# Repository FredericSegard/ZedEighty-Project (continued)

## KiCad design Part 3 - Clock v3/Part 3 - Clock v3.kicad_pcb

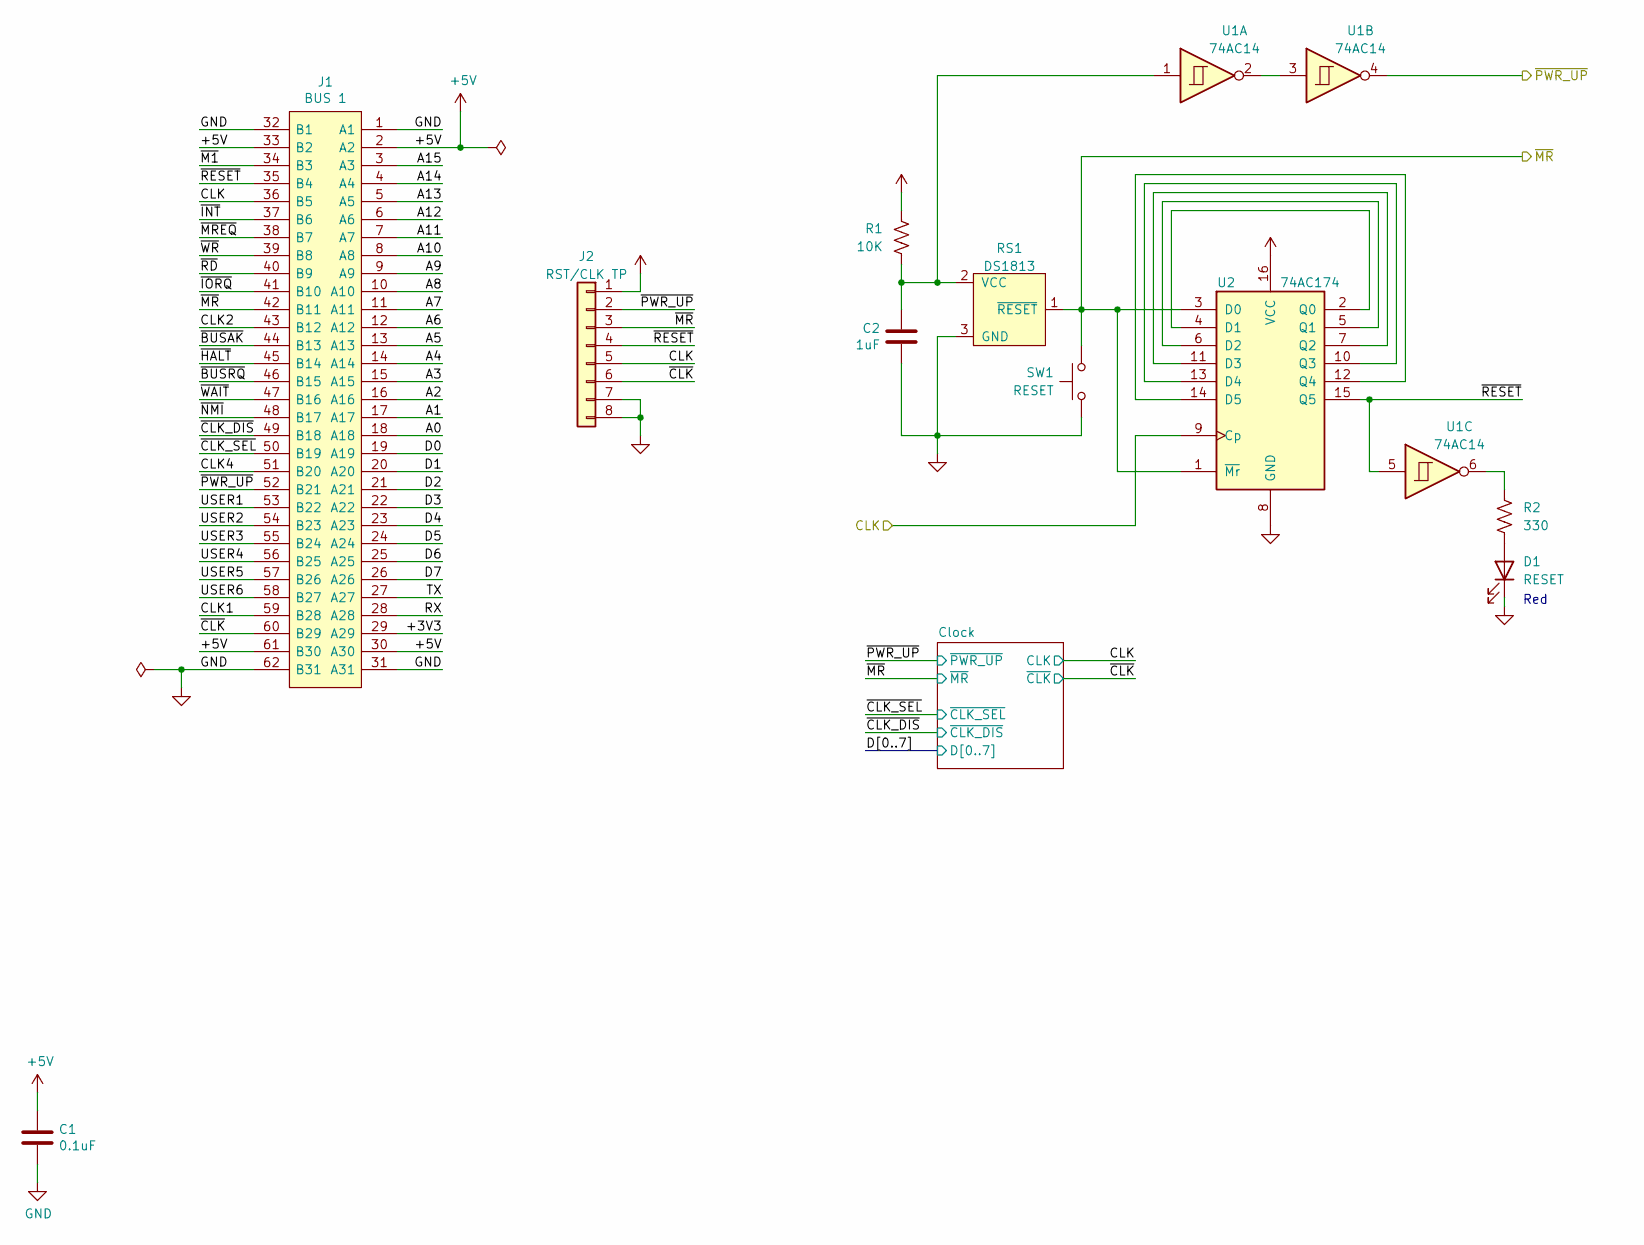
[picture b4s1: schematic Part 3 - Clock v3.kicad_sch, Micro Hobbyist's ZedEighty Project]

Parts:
C1: 0.1uF; C_Disc_D3.0mm_W2.0mm_P2.50mm
C2: 1uF; C_Disc_D3.0mm_W2.0mm_P2.50mm
D1: RESET; LED_D3.0mm_Horizontal_O1.27mm_Z2.0mm_Clear
J1: BUS 1; BUS_XT; Mouser Part Number 571-6-5530843-5
J2: RST/CLK TP; PinHeader_1x08_P2.54mm_Horizontal
R1: 10K; R_Axial_DIN0207_L6.3mm_D2.5mm_P10.16mm_Horizontal
R2: 330; R_Axial_DIN0207_L6.3mm_D2.5mm_P10.16mm_Horizontal
RS1: DS1813; TO-92L_Inline_Wide
SW1: RESET; SW_Tactile_SPST_Angled_PTS645Vx58-2LFS
U1: 74AC14; DIP-14_W7.62mm_Socket
U2: 74AC174; DIP-16_W7.62mm_Socket

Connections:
/+3V3: J1.29 (A29)
/A0: J1.18 (A18)
/A1: J1.17 (A17)
/A2: J1.16 (A16)
/A3: J1.15 (A15)
/A4: J1.14 (A14)
/A5: J1.13 (A13)
/A6: J1.12 (A12)
/A7: J1.11 (A11)
/A8: J1.10 (A10)
/A9: J1.9 (A9)
/A10: J1.8 (A8)
/A11: J1.7 (A7)
/A12: J1.6 (A6)
/A13: J1.5 (A5)
/A14: J1.4 (A4)
/A15: J1.3 (A3)
/CLK: J1.36 (B5), J2.5, U2.9 (Cp); also elsewhere on the board
/CLK1: J1.59 (B28)
/CLK2: J1.43 (B12)
/CLK4: J1.51 (B20)
/D0: J1.19 (A19); also elsewhere on the board
/D1: J1.20 (A20); also elsewhere on the board
/D2: J1.21 (A21)
/D3: J1.22 (A22)
/D4: J1.23 (A23)
/D5: J1.24 (A24)
/D6: J1.25 (A25)
/D7: J1.26 (A26)
/RX: J1.28 (A28)
/TX: J1.27 (A27)
/USER1: J1.53 (B22)
/USER2: J1.54 (B23)
/USER3: J1.55 (B24)
/USER4: J1.56 (B25)
/USER5: J1.57 (B26)
/USER6: J1.58 (B27)
/~BUSAK: J1.44 (B13)
/~BUSRQ: J1.46 (B15)
/~CLK_DIS: J1.49 (B18); also elsewhere on the board
/~CLK_SEL: J1.50 (B19); also elsewhere on the board
/~CLK: J1.60 (B29), J2.6; also elsewhere on the board
/~HALT: J1.45 (B14)
/~INT: J1.37 (B6)
/~IORQ: J1.41 (B10)
/~M1: J1.34 (B3)
/~MREQ: J1.38 (B7)
/~MR: J1.42 (B11), J2.3, RS1.1 (~RESET), SW1.1, U2.1 (~Mr), U2.3 (D0); also elsewhere on the board
/~NMI: J1.48 (B17)
/~PWR_UP: J1.52 (B21), J2.2, U1.4; also elsewhere on the board
/~RD: J1.40 (B9)
/~RESET: J1.35 (B4), J2.4, U1.5, U2.15 (Q5)
/~WAIT: J1.47 (B16)
/~WR: J1.39 (B8)
unnamed: C2.1, R1.1, RS1.2 (VCC), U1.1
unnamed: D1.2 (A), R2.2
unnamed: R2.1, U1.6
unnamed: U1.2, U1.3
unnamed: U2.2 (Q0), U2.4 (D1)
unnamed: U2.5 (Q1), U2.6 (D2)
unnamed: U2.10 (Q3), U2.13 (D4)
unnamed: U2.7 (Q2), U2.11 (D3)
unnamed: U2.12 (Q4), U2.14 (D5)

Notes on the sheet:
Red

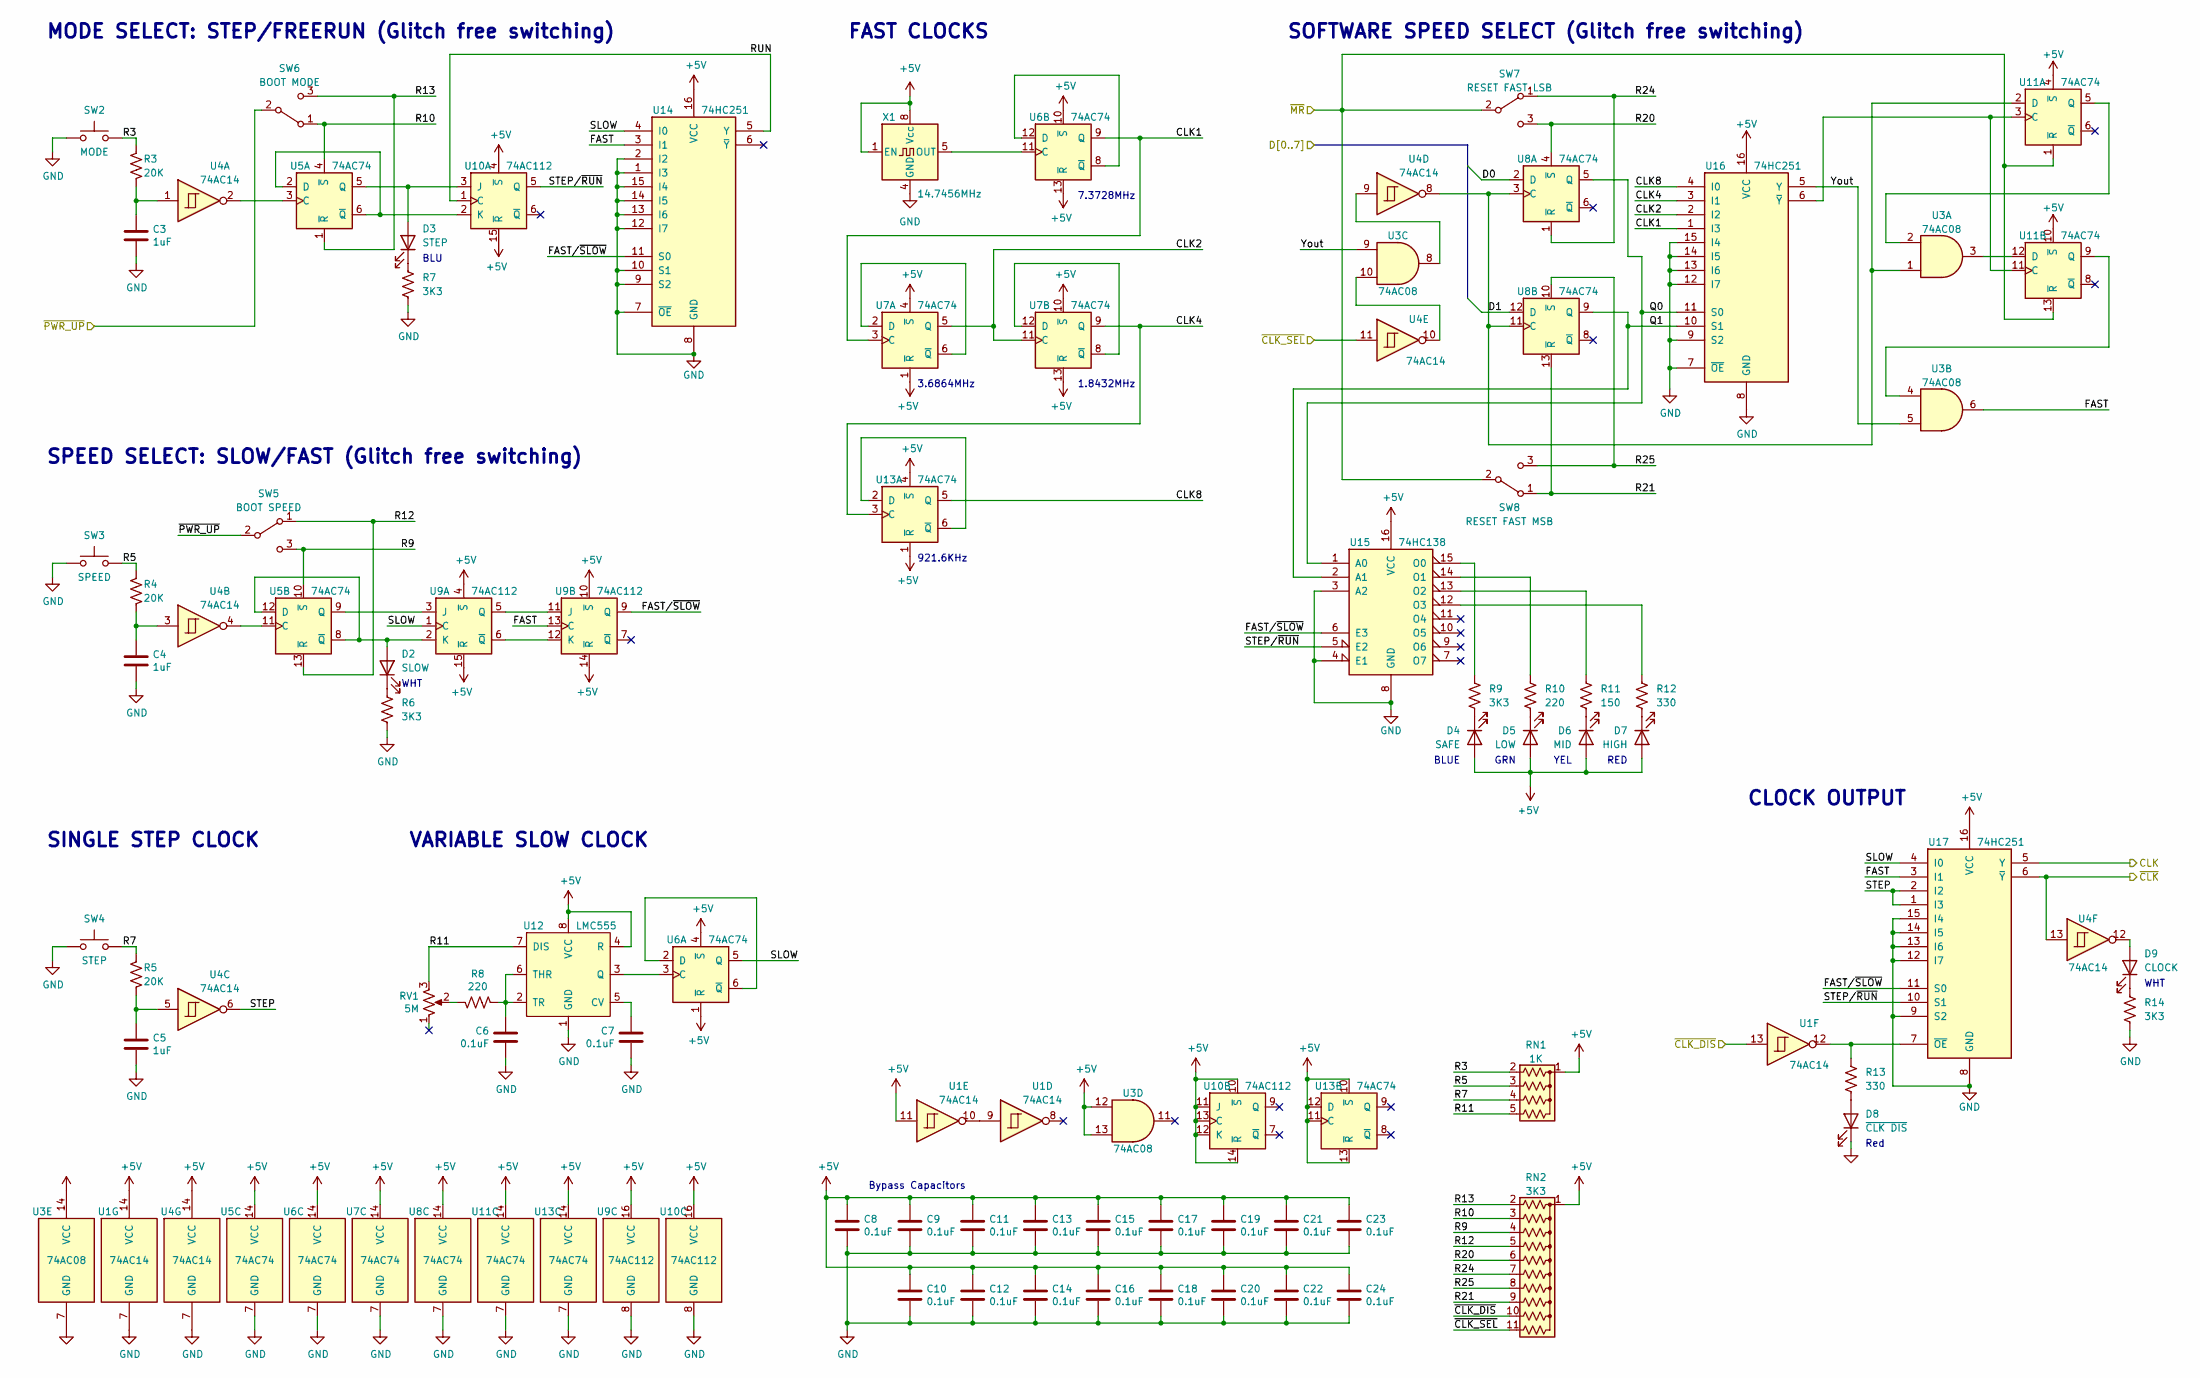
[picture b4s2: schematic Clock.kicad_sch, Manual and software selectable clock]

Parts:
C3, C4, C5: 1uF; C_Disc_D3.0mm_W1.6mm_P2.50mm
C6, C7, C8, C9, C10, C11, C12, C13, C14, C15, C16, C17, C18, C19, C20, C21, C22, C23, C24: 0.1uF; C_Disc_D3.0mm_W1.6mm_P2.50mm
D2: SLOW; LED_D3.0mm_Horizontal_O1.27mm_Z2.0mm_Clear
D3: STEP; LED_D3.0mm_Horizontal_O1.27mm_Z2.0mm_Clear
D4: SAFE; LED_D3.0mm_Horizontal_O1.27mm_Z2.0mm_Clear
D5: LOW; LED_D3.0mm_Horizontal_O1.27mm_Z2.0mm_Clear
D6: MID; LED_D3.0mm_Horizontal_O1.27mm_Z2.0mm_Clear
D7: HIGH; LED_D3.0mm_Horizontal_O1.27mm_Z2.0mm_Clear
D8: ~{CLK DIS}; LED_D3.0mm_Horizontal_O1.27mm_Z2.0mm_Clear
D9: CLOCK; LED_D3.0mm_Horizontal_O1.27mm_Z2.0mm_Clear
R3, R4, R5: 20K; R_Axial_DIN0207_L6.3mm_D2.5mm_P10.16mm_Horizontal
R6, R7, R9, R14: 3K3; R_Axial_DIN0207_L6.3mm_D2.5mm_P10.16mm_Horizontal
R8, R10: 220; R_Axial_DIN0207_L6.3mm_D2.5mm_P10.16mm_Horizontal
R11: 150; R_Axial_DIN0207_L6.3mm_D2.5mm_P10.16mm_Horizontal
R12, R13: 330; R_Axial_DIN0207_L6.3mm_D2.5mm_P10.16mm_Horizontal
RN1: 1K; R_Array_SIP5
RN2: 3K3; R_Array_SIP11
RV1: 5M; Potentiometer_Bourns_3296Z_Horizontal
SW2: MODE; SW_Tactile_SPST_Angled_PTS645Vx58-2LFS
SW3: SPEED; SW_Tactile_SPST_Angled_PTS645Vx58-2LFS
SW4: STEP; SW_Tactile_SPST_Angled_PTS645Vx58-2LFS
SW5: BOOT SPEED; Microswitch_4.7mm_spacing
SW6: BOOT MODE; Microswitch_4.7mm_spacing
SW7: RESET FAST LSB; Microswitch_4.7mm_spacing
SW8: RESET FAST MSB; Microswitch_4.7mm_spacing
U1, U4: 74AC14; DIP-14_W7.62mm_Socket
U3: 74AC08; DIP-14_W7.62mm_Socket
U5, U6, U7, U8, U11, U13: 74AC74; DIP-14_W7.62mm_Socket
U9, U10: 74AC112; DIP-16_W7.62mm_Socket
U12: LMC555; DIP-8_W7.62mm_Socket
U14, U16, U17: 74HC251; DIP-16_W7.62mm_Socket
U15: 74HC138; DIP-16_W7.62mm_Socket
X1: 14.7456MHz; DIP-8-4_W7.62mm_Oscillator_Socket

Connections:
/CLK: U17.5 (Y); also elsewhere on the board
/Clock/CLK1: U6.9 (Q), U7.3 (C), U16.1 (I3)
/Clock/CLK2: U7.5 (Q), U7.11 (C), U16.2 (I2)
/Clock/CLK4: U7.9 (Q), U13.3 (C), U16.3 (I1)
/Clock/CLK8: U13.5 (Q), U16.4 (I0)
/Clock/FAST: U3.6, U9.13 (C), U14.3 (I1), U17.3 (I1)
/Clock/FAST/~SLOW: U9.9 (Q), U14.11 (S0), U15.6 (E3), U17.11 (S0)
/Clock/Q0: U8.5 (Q), U15.1 (A0), U16.11 (S0)
/Clock/Q1: U8.9 (Q), U15.2 (A1), U16.10 (S1)
/Clock/R3: R3.2, RN1.2 (R1), SW2.1
/Clock/R5: R4.2, RN1.3 (R2), SW3.1
/Clock/R7: R5.2, RN1.4 (R3), SW4.1
/Clock/R9: RN2.4 (R3), SW5.3 (C), U5.10 (~S)
/Clock/R10: RN2.3 (R2), SW6.1 (A), U5.4 (~S)
/Clock/R11: RN1.5 (R4), RV1.3, U12.7 (DIS)
/Clock/R12: RN2.5 (R4), SW5.1 (A), U5.13 (~R)
/Clock/R13: RN2.2 (R1), SW6.3 (C), U5.1 (~R)
/Clock/R20: RN2.6 (R5), SW7.3 (C), U8.4 (~S)
/Clock/R21: RN2.9 (R8), SW8.1 (A), U8.13 (~R)
/Clock/R24: RN2.7 (R6), SW7.1 (A), U8.1 (~R)
/Clock/R25: RN2.8 (R7), SW8.3 (C), U8.10 (~S)
/Clock/RUN: U10.1 (C), U14.5 (Y)
/Clock/SLOW: U6.5 (Q), U9.1 (C), U14.4 (I0), U17.4 (I0)
/Clock/STEP: U4.6, U17.1 (I3), U17.2 (I2)
/Clock/STEP/~RUN: U10.5 (Q), U15.5 (E2), U17.10 (S1)
/Clock/Yout: U3.5, U3.9, U16.5 (Y)
/D0: U8.2 (D); also elsewhere on the board
/D1: U8.12 (D); also elsewhere on the board
/~CLK_DIS: RN2.10 (R9), U1.13; also elsewhere on the board
/~CLK_SEL: RN2.11 (R10), U4.11; also elsewhere on the board
/~CLK: U4.13, U17.6 (~Y); also elsewhere on the board
/~MR: SW7.2 (B), SW8.2 (B), U11.1 (~R), U11.13 (~R); also elsewhere on the board
/~PWR_UP: SW5.2 (B), SW6.2 (B); also elsewhere on the board
unnamed: C3.1, R3.1, U4.1
unnamed: C4.1, R4.1, U4.3
unnamed: C5.1, R5.1, U4.5
unnamed: C6.1, R8.2, U12.2 (TR), U12.6 (THR)
unnamed: C7.1, U12.5 (CV)
unnamed: D2.1 (K), R6.1
unnamed: D2.2 (A), U5.8 (~Q), U5.12 (D), U9.2 (K)
unnamed: D3.1 (K), R7.1
unnamed: D3.2 (A), U5.5 (Q), U10.3 (J)
unnamed: D4.1 (K), R9.2
unnamed: D5.1 (K), R10.2
unnamed: D6.1 (K), R11.2
unnamed: D7.1 (K), R12.2
unnamed: D8.2 (A), R13.2
unnamed: D9.1 (K), R14.1
unnamed: D9.2 (A), U4.12
unnamed: R8.1, RV1.2
unnamed: R9.1, U15.15 (O0)
unnamed: R10.1, U15.14 (O1)
unnamed: R11.1, U15.13 (O2)
unnamed: R12.1, U15.12 (O3)
unnamed: R13.1, U1.12, U17.7 (~OE)
unnamed: U1.9, U1.10
unnamed: U3.8, U4.9
unnamed: U3.10, U4.10
unnamed: U4.2, U5.3 (C)
unnamed: U4.4, U5.11 (C)
unnamed: U5.9 (Q), U9.3 (J)
unnamed: U6.2 (D), U6.6 (~Q)
unnamed: U6.11 (C), X1.5 (OUT)
unnamed: U6.8 (~Q), U6.12 (D)
unnamed: U7.2 (D), U7.6 (~Q)
unnamed: U7.8 (~Q), U7.12 (D)
unnamed: U9.5 (Q), U9.11 (J)
unnamed: U9.6 (~Q), U9.12 (K)
unnamed: U5.2 (D), U5.6 (~Q), U10.2 (K)
unnamed: U3.1, U4.8, U8.3 (C), U8.11 (C), U11.2 (D)
unnamed: U3.2, U11.5 (Q)
unnamed: U3.4, U11.9 (Q)
unnamed: U11.3 (C), U11.11 (C), U16.6 (~Y)
unnamed: U3.3, U11.12 (D)
unnamed: U6.3 (C), U12.3 (Q)
unnamed: U13.2 (D), U13.6 (~Q)

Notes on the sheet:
3.6864MHz
VARIABLE SLOW CLOCK
SPEED SELECT: SLOW/FAST (Glitch free switching)
Bypass Capacitors
MODE SELECT: STEP/FREERUN (Glitch free switching)
RED
FAST CLOCKS
SOFTWARE SPEED SELECT (Glitch free switching)
CLOCK OUTPUT
921.6KHz
GRN
WHT
1.8432MHz
BLU
Red
7.3728MHz
YEL
BLUE
SINGLE STEP CLOCK

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
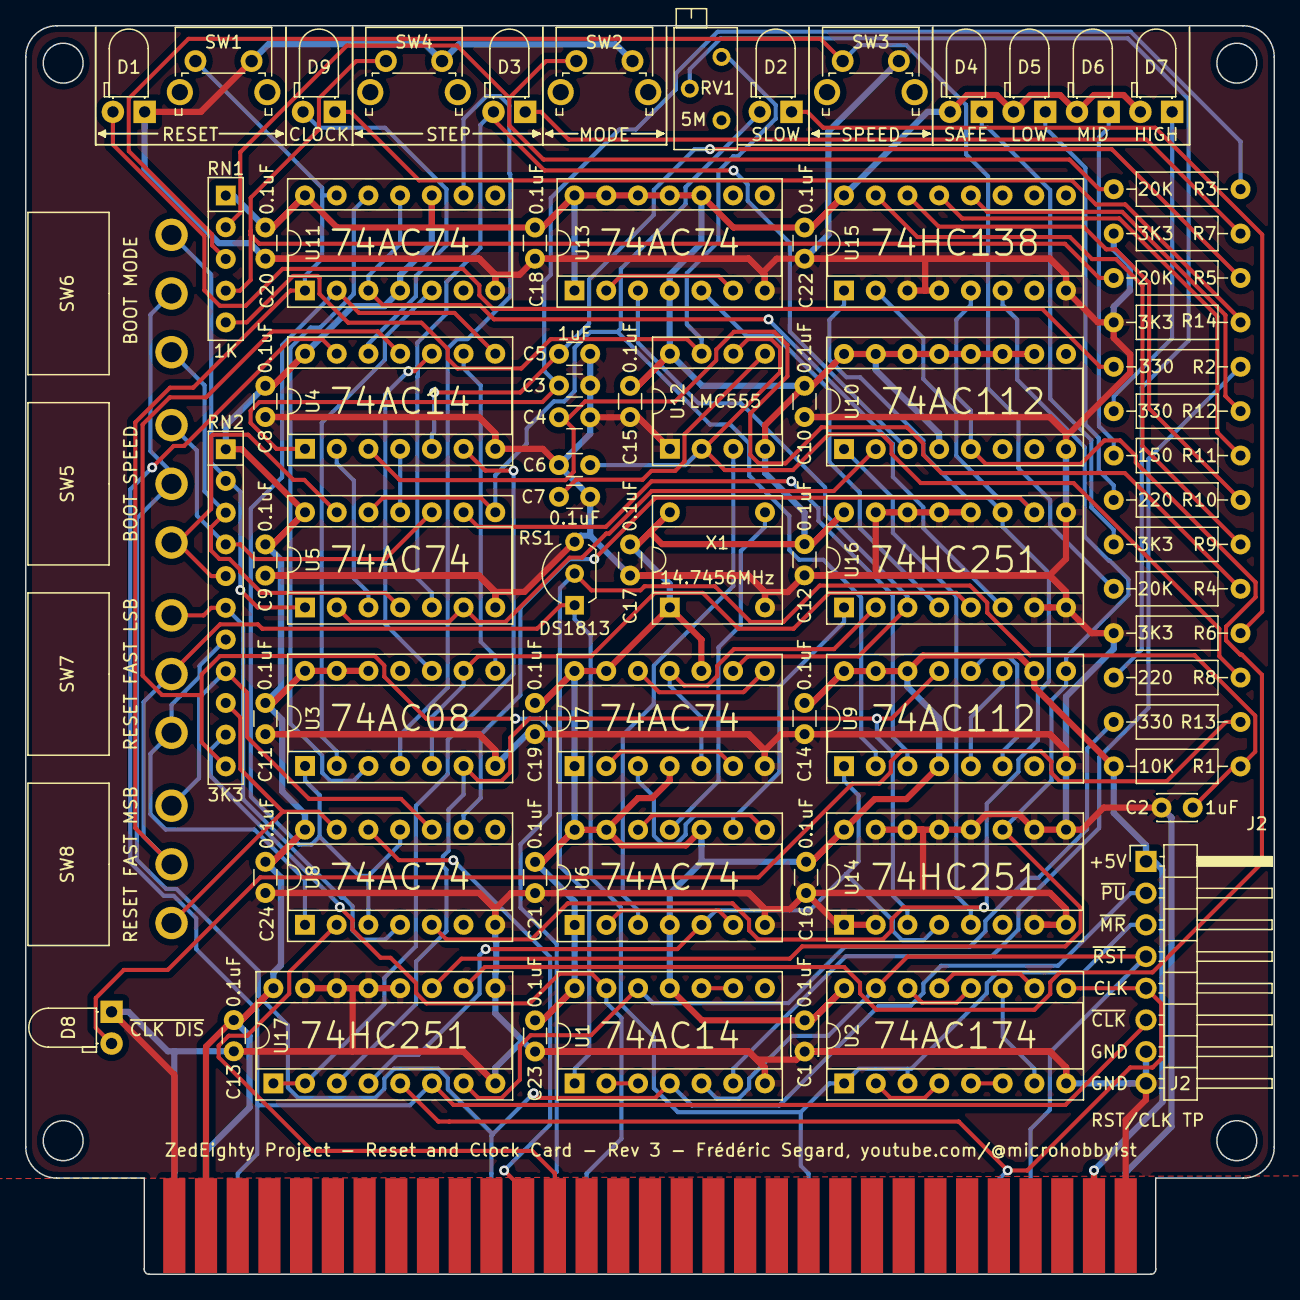
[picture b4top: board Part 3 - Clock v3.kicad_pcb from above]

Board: 2 copper layers, 100.0 x 100.0 mm, 79 parts (0 on the bottom side), 88 nets.

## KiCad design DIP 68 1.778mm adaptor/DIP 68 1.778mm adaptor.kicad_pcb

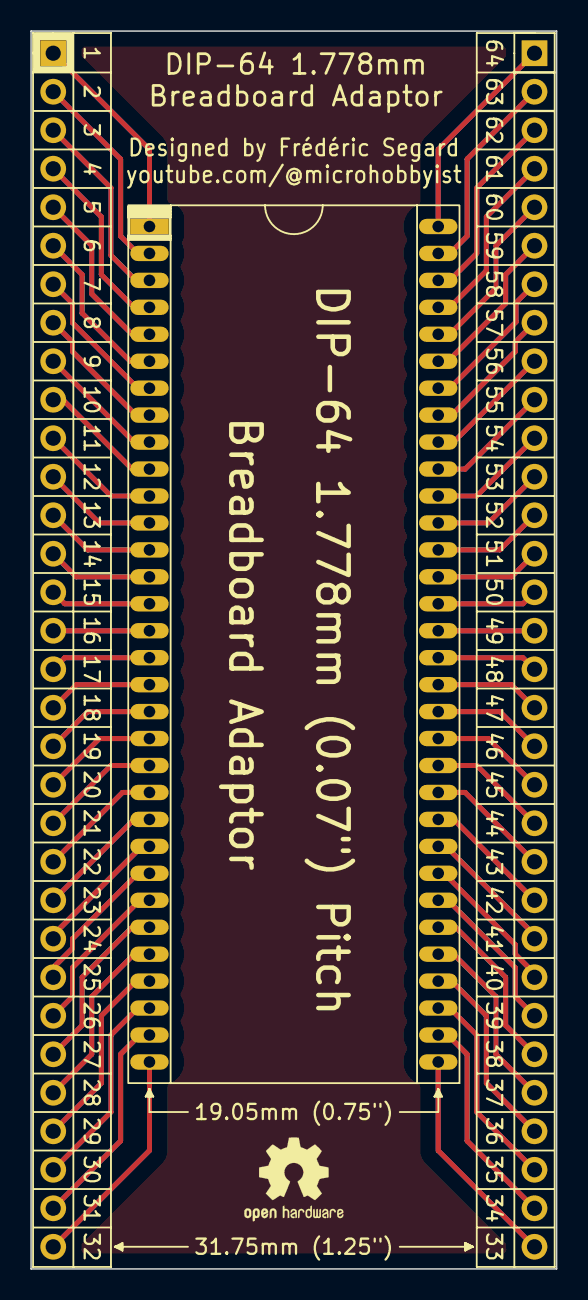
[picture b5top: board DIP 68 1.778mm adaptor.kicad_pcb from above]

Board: 2 copper layers, 34.7 x 81.7 mm, 4 parts (0 on the bottom side), 64 nets.

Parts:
J1, J2: Header; PinHeader_1x32_P2.54mm_Vertical
REF1: OSHW-Logo2_7.3x6mm_SilkScreen
U1: DIP-64; DIP 64 1.778 pitch

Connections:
/1: J1.1, U1.1 (GND)
/2: J1.2, U1.2 (~DHCLK)
/3: J1.3, U1.3 (~{DLCLK)
/4: J1.4, U1.4 (~VRESET)
/5: J1.5, U1.5 (~HSYNC)
/6: J1.6, U1.6 (~CSYNC)
/7: J1.7, U1.7 (BLEO)
/8: J1.8, U1.8 (CPUCK/~VDS)
/9: J1.9, U1.9 (~RESET)
/10: J1.10, U1.10 (~YS)
/11: J1.11, U1.11 (CBDR)
/12: J1.12, U1.12 (C7)
/13: J1.13, U1.13 (C6)
/14: J1.14, U1.14 (C5)
/15: J1.15, U1.15 (C4)
/16: J1.16, U1.16 (C3)
/17: J1.17, U1.17 (C2)
/18: J1.18, U1.18 (C1)
/19: J1.19, U1.19 (C0)
/20: J1.20, U1.20 (GND_DAC)
/21: J1.21, U1.21 (VCC_DAC)
/22: J1.22, U1.22 (G)
/23: J1.23, U1.23 (R)
/24: J1.24, U1.24 (B)
/25: J1.25, U1.25 (~INT)
/26: J1.26, U1.26 (~WAIT)
/27: J1.27, U1.27 (~HRESET)
/28: J1.28, U1.28 (MODE_1)
/29: J1.29, U1.29 (MODE_0)
/30: J1.30, U1.30 (~CSW)
/31: J1.31, U1.31 (~CSR)
/32: J1.32, U1.32 (D7)
/33: J2.32, U1.33 (VBB)
/34: J2.31, U1.34 (D6)
/35: J2.30, U1.35 (D5)
/36: J2.29, U1.36 (D4)
/37: J2.28, U1.37 (D3)
/38: J2.27, U1.38 (D2)
/39: J2.26, U1.39 (D1)
/40: J2.25, U1.40 (D0)
/41: J2.24, U1.41 (RD0)
/42: J2.23, U1.42 (RD1)
/43: J2.22, U1.43 (RD2)
/44: J2.21, U1.44 (RD3)
/45: J2.20, U1.45 (RD4)
/46: J2.19, U1.46 (RD5)
/47: J2.18, U1.47 (RD6)
/48: J2.17, U1.48 (RD7)
/49: J2.16, U1.49 (AD0)
/50: J2.15, U1.50 (AD1)
/51: J2.14, U1.51 (AD2)
/52: J2.13, U1.52 (AD3)
/53: J2.12, U1.53 (AD4)
/54: J2.11, U1.54 (AD5)
/55: J2.10, U1.55 (AD6)
/56: J2.9, U1.56 (AD7)
/57: J2.8, U1.57 (R/~W)
/58: J2.7, U1.58 (VCC)
/59: J2.6, U1.59 (~CASX)
/60: J2.5, U1.60 (~CAS1)
/61: J2.4, U1.61 (~CAS0)
/62: J2.3, U1.62 (~RAS)
/63: J2.2, U1.63 (XTAL1)
/64: J2.1, U1.64 (XTAL2)

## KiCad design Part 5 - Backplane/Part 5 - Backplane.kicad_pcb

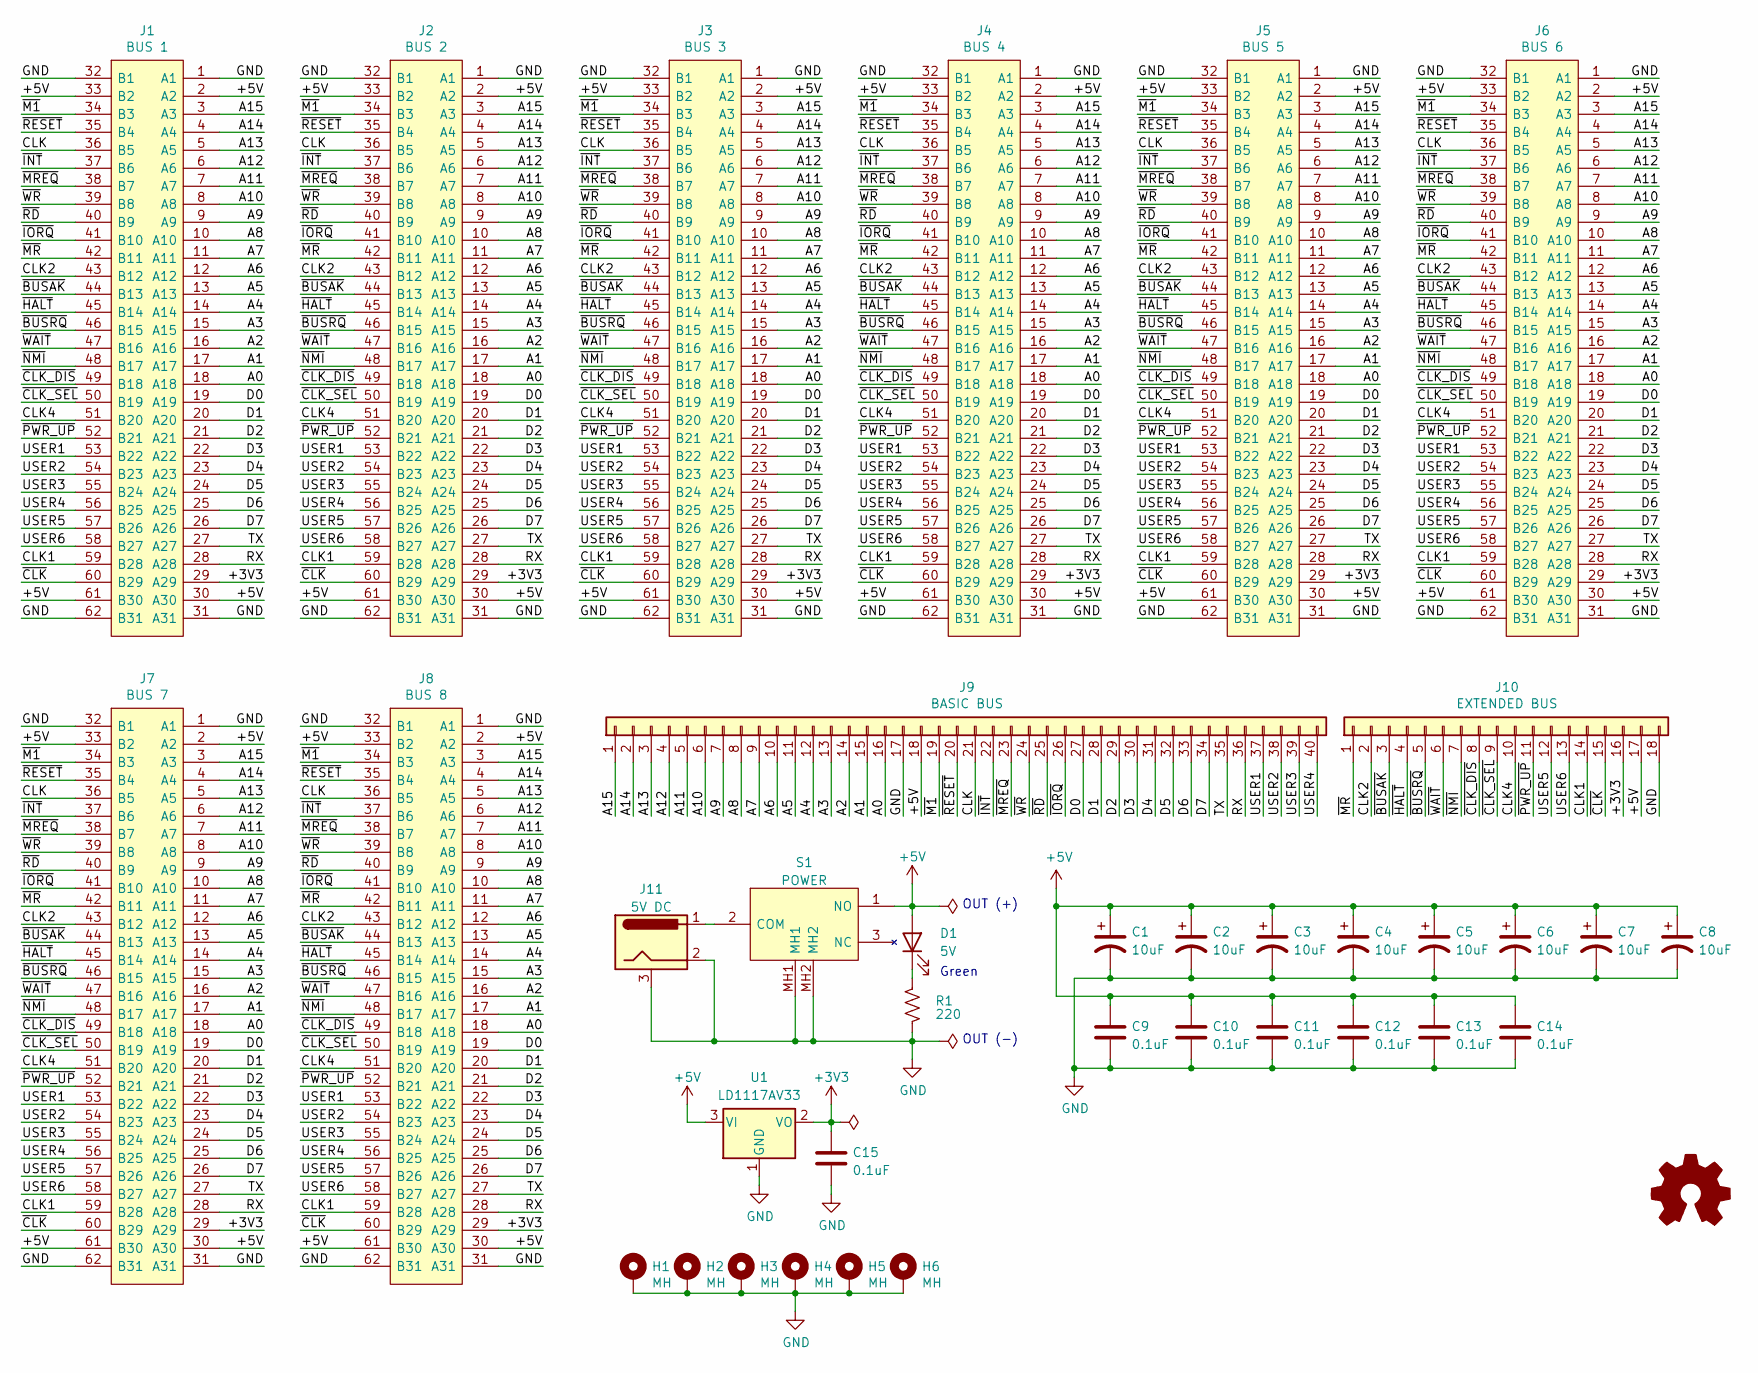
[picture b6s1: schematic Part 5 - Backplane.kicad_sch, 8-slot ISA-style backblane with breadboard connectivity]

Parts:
C1, C2, C3, C4, C5, C6, C7, C8: 10uF; CP_Radial_D6.3mm_P2.50mm
C9, C10, C11, C12, C13, C14, C15: 0.1uF; C_Disc_D3.0mm_W2.0mm_P2.50mm
D1: 5V; LED_D3.0mm
H1, H2, H3, H4, H5, H6: MH; MountingHole_3.2mm_M3_Pad_Via
J1: BUS 1; ISA_Connector; Mouser Part Number 571-6-5530843-5
J2: BUS 2; ISA_Connector; Mouser Part Number 571-6-5530843-5
J3: BUS 3; ISA_Connector; Mouser Part Number 571-6-5530843-5
J4: BUS 4; ISA_Connector; Mouser Part Number 571-6-5530843-5
J5: BUS 5; ISA_Connector; Mouser Part Number 571-6-5530843-5
J6: BUS 6; ISA_Connector; Mouser Part Number 571-6-5530843-5
J7: BUS 7; ISA_Connector; Mouser Part Number 571-6-5530843-5
J8: BUS 8; ISA_Connector; Mouser Part Number 571-6-5530843-5
J9: BASIC BUS; PinHeader_1x40_P2.54mm_Vertical
J10: EXTENDED BUS; PinHeader_1x18_P2.54mm_Vertical
J11: 5V DC; BarrelJack_Horizontal
R1: 220; R_Axial_DIN0207_L6.3mm_D2.5mm_P10.16mm_Horizontal
S1: POWER; SPDT_NKK_SWITCH_M2012S2A2W30; Manufacturer_Part_Number M2012S2A2W30; Mouser Part Number 633-M2012S2A2W30
U1: LD1117AV33; TO-220-3_Horizontal_TabDown

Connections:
+3V3: C15.1, J1.29 (A29), J2.29 (A29), J3.29 (A29), J4.29 (A29), J5.29 (A29), J6.29 (A29), J7.29 (A29), J8.29 (A29), J10.16, U1.2 (VO)
+5V: C1.1, C2.1, C3.1, C4.1, C5.1, C6.1, C7.1, C8.1, C9.1, C10.1, C11.1, C12.1, C13.1, C14.1, D1.2 (A), J1.2 (A2), J1.30 (A30), J1.33 (B2), J1.61 (B30), J2.2 (A2), J2.30 (A30), J2.33 (B2), J2.61 (B30), J3.2 (A2), J3.30 (A30), J3.33 (B2), J3.61 (B30), J4.2 (A2), J4.30 (A30), J4.33 (B2), J4.61 (B30), J5.2 (A2), J5.30 (A30), J5.33 (B2), J5.61 (B30), J6.2 (A2), J6.30 (A30), J6.33 (B2), J6.61 (B30), J7.2 (A2), J7.30 (A30), J7.33 (B2), J7.61 (B30), J8.2 (A2), J8.30 (A30), J8.33 (B2), J8.61 (B30), J9.18, J10.17, S1.1 (NO), U1.3 (VI)
/A0: J1.18 (A18), J2.18 (A18), J3.18 (A18), J4.18 (A18), J5.18 (A18), J6.18 (A18), J7.18 (A18), J8.18 (A18), J9.16
/A1: J1.17 (A17), J2.17 (A17), J3.17 (A17), J4.17 (A17), J5.17 (A17), J6.17 (A17), J7.17 (A17), J8.17 (A17), J9.15
/A2: J1.16 (A16), J2.16 (A16), J3.16 (A16), J4.16 (A16), J5.16 (A16), J6.16 (A16), J7.16 (A16), J8.16 (A16), J9.14
/A3: J1.15 (A15), J2.15 (A15), J3.15 (A15), J4.15 (A15), J5.15 (A15), J6.15 (A15), J7.15 (A15), J8.15 (A15), J9.13
/A4: J1.14 (A14), J2.14 (A14), J3.14 (A14), J4.14 (A14), J5.14 (A14), J6.14 (A14), J7.14 (A14), J8.14 (A14), J9.12
/A5: J1.13 (A13), J2.13 (A13), J3.13 (A13), J4.13 (A13), J5.13 (A13), J6.13 (A13), J7.13 (A13), J8.13 (A13), J9.11
/A6: J1.12 (A12), J2.12 (A12), J3.12 (A12), J4.12 (A12), J5.12 (A12), J6.12 (A12), J7.12 (A12), J8.12 (A12), J9.10
/A7: J1.11 (A11), J2.11 (A11), J3.11 (A11), J4.11 (A11), J5.11 (A11), J6.11 (A11), J7.11 (A11), J8.11 (A11), J9.9
/A8: J1.10 (A10), J2.10 (A10), J3.10 (A10), J4.10 (A10), J5.10 (A10), J6.10 (A10), J7.10 (A10), J8.10 (A10), J9.8
/A9: J1.9 (A9), J2.9 (A9), J3.9 (A9), J4.9 (A9), J5.9 (A9), J6.9 (A9), J7.9 (A9), J8.9 (A9), J9.7
/A10: J1.8 (A8), J2.8 (A8), J3.8 (A8), J4.8 (A8), J5.8 (A8), J6.8 (A8), J7.8 (A8), J8.8 (A8), J9.6
/A11: J1.7 (A7), J2.7 (A7), J3.7 (A7), J4.7 (A7), J5.7 (A7), J6.7 (A7), J7.7 (A7), J8.7 (A7), J9.5
/A12: J1.6 (A6), J2.6 (A6), J3.6 (A6), J4.6 (A6), J5.6 (A6), J6.6 (A6), J7.6 (A6), J8.6 (A6), J9.4
/A13: J1.5 (A5), J2.5 (A5), J3.5 (A5), J4.5 (A5), J5.5 (A5), J6.5 (A5), J7.5 (A5), J8.5 (A5), J9.3
/A14: J1.4 (A4), J2.4 (A4), J3.4 (A4), J4.4 (A4), J5.4 (A4), J6.4 (A4), J7.4 (A4), J8.4 (A4), J9.2
/A15: J1.3 (A3), J2.3 (A3), J3.3 (A3), J4.3 (A3), J5.3 (A3), J6.3 (A3), J7.3 (A3), J8.3 (A3), J9.1
/CLK: J1.36 (B5), J2.36 (B5), J3.36 (B5), J4.36 (B5), J5.36 (B5), J6.36 (B5), J7.36 (B5), J8.36 (B5), J9.21
/CLK1: J1.59 (B28), J2.59 (B28), J3.59 (B28), J4.59 (B28), J5.59 (B28), J6.59 (B28), J7.59 (B28), J8.59 (B28), J10.14
/CLK2: J1.43 (B12), J2.43 (B12), J3.43 (B12), J4.43 (B12), J5.43 (B12), J6.43 (B12), J7.43 (B12), J8.43 (B12), J10.2
/CLK4: J1.51 (B20), J2.51 (B20), J3.51 (B20), J4.51 (B20), J5.51 (B20), J6.51 (B20), J7.51 (B20), J8.51 (B20), J10.10
/D0: J1.19 (A19), J2.19 (A19), J3.19 (A19), J4.19 (A19), J5.19 (A19), J6.19 (A19), J7.19 (A19), J8.19 (A19), J9.27
/D1: J1.20 (A20), J2.20 (A20), J3.20 (A20), J4.20 (A20), J5.20 (A20), J6.20 (A20), J7.20 (A20), J8.20 (A20), J9.28
/D2: J1.21 (A21), J2.21 (A21), J3.21 (A21), J4.21 (A21), J5.21 (A21), J6.21 (A21), J7.21 (A21), J8.21 (A21), J9.29
/D3: J1.22 (A22), J2.22 (A22), J3.22 (A22), J4.22 (A22), J5.22 (A22), J6.22 (A22), J7.22 (A22), J8.22 (A22), J9.30
/D4: J1.23 (A23), J2.23 (A23), J3.23 (A23), J4.23 (A23), J5.23 (A23), J6.23 (A23), J7.23 (A23), J8.23 (A23), J9.31
/D5: J1.24 (A24), J2.24 (A24), J3.24 (A24), J4.24 (A24), J5.24 (A24), J6.24 (A24), J7.24 (A24), J8.24 (A24), J9.32
/D6: J1.25 (A25), J2.25 (A25), J3.25 (A25), J4.25 (A25), J5.25 (A25), J6.25 (A25), J7.25 (A25), J8.25 (A25), J9.33
/D7: J1.26 (A26), J2.26 (A26), J3.26 (A26), J4.26 (A26), J5.26 (A26), J6.26 (A26), J7.26 (A26), J8.26 (A26), J9.34
/RX: J1.28 (A28), J2.28 (A28), J3.28 (A28), J4.28 (A28), J5.28 (A28), J6.28 (A28), J7.28 (A28), J8.28 (A28), J9.36
/TX: J1.27 (A27), J2.27 (A27), J3.27 (A27), J4.27 (A27), J5.27 (A27), J6.27 (A27), J7.27 (A27), J8.27 (A27), J9.35
/USER1: J1.53 (B22), J2.53 (B22), J3.53 (B22), J4.53 (B22), J5.53 (B22), J6.53 (B22), J7.53 (B22), J8.53 (B22), J9.37
/USER2: J1.54 (B23), J2.54 (B23), J3.54 (B23), J4.54 (B23), J5.54 (B23), J6.54 (B23), J7.54 (B23), J8.54 (B23), J9.38
/USER3: J1.55 (B24), J2.55 (B24), J3.55 (B24), J4.55 (B24), J5.55 (B24), J6.55 (B24), J7.55 (B24), J8.55 (B24), J9.39
/USER4: J1.56 (B25), J2.56 (B25), J3.56 (B25), J4.56 (B25), J5.56 (B25), J6.56 (B25), J7.56 (B25), J8.56 (B25), J9.40
/USER5: J1.57 (B26), J2.57 (B26), J3.57 (B26), J4.57 (B26), J5.57 (B26), J6.57 (B26), J7.57 (B26), J8.57 (B26), J10.12
/USER6: J1.58 (B27), J2.58 (B27), J3.58 (B27), J4.58 (B27), J5.58 (B27), J6.58 (B27), J7.58 (B27), J8.58 (B27), J10.13
/~BUSAK: J1.44 (B13), J2.44 (B13), J3.44 (B13), J4.44 (B13), J5.44 (B13), J6.44 (B13), J7.44 (B13), J8.44 (B13), J10.3
/~BUSRQ: J1.46 (B15), J2.46 (B15), J3.46 (B15), J4.46 (B15), J5.46 (B15), J6.46 (B15), J7.46 (B15), J8.46 (B15), J10.5
/~CLK_DIS: J1.49 (B18), J2.49 (B18), J3.49 (B18), J4.49 (B18), J5.49 (B18), J6.49 (B18), J7.49 (B18), J8.49 (B18), J10.8
/~CLK_SEL: J1.50 (B19), J2.50 (B19), J3.50 (B19), J4.50 (B19), J5.50 (B19), J6.50 (B19), J7.50 (B19), J8.50 (B19), J10.9
/~CLK: J1.60 (B29), J2.60 (B29), J3.60 (B29), J4.60 (B29), J5.60 (B29), J6.60 (B29), J7.60 (B29), J8.60 (B29), J10.15
/~HALT: J1.45 (B14), J2.45 (B14), J3.45 (B14), J4.45 (B14), J5.45 (B14), J6.45 (B14), J7.45 (B14), J8.45 (B14), J10.4
/~INT: J1.37 (B6), J2.37 (B6), J3.37 (B6), J4.37 (B6), J5.37 (B6), J6.37 (B6), J7.37 (B6), J8.37 (B6), J9.22
/~IORQ: J1.41 (B10), J2.41 (B10), J3.41 (B10), J4.41 (B10), J5.41 (B10), J6.41 (B10), J7.41 (B10), J8.41 (B10), J9.26
/~M1: J1.34 (B3), J2.34 (B3), J3.34 (B3), J4.34 (B3), J5.34 (B3), J6.34 (B3), J7.34 (B3), J8.34 (B3), J9.19
/~MREQ: J1.38 (B7), J2.38 (B7), J3.38 (B7), J4.38 (B7), J5.38 (B7), J6.38 (B7), J7.38 (B7), J8.38 (B7), J9.23
/~MR: J1.42 (B11), J2.42 (B11), J3.42 (B11), J4.42 (B11), J5.42 (B11), J6.42 (B11), J7.42 (B11), J8.42 (B11), J10.1
/~NMI: J1.48 (B17), J2.48 (B17), J3.48 (B17), J4.48 (B17), J5.48 (B17), J6.48 (B17), J7.48 (B17), J8.48 (B17), J10.7
/~PWR_UP: J1.52 (B21), J2.52 (B21), J3.52 (B21), J4.52 (B21), J5.52 (B21), J6.52 (B21), J7.52 (B21), J8.52 (B21), J10.11
/~RD: J1.40 (B9), J2.40 (B9), J3.40 (B9), J4.40 (B9), J5.40 (B9), J6.40 (B9), J7.40 (B9), J8.40 (B9), J9.25
/~RESET: J1.35 (B4), J2.35 (B4), J3.35 (B4), J4.35 (B4), J5.35 (B4), J6.35 (B4), J7.35 (B4), J8.35 (B4), J9.20
/~WAIT: J1.47 (B16), J2.47 (B16), J3.47 (B16), J4.47 (B16), J5.47 (B16), J6.47 (B16), J7.47 (B16), J8.47 (B16), J10.6
/~WR: J1.39 (B8), J2.39 (B8), J3.39 (B8), J4.39 (B8), J5.39 (B8), J6.39 (B8), J7.39 (B8), J8.39 (B8), J9.24
GND: C1.2, C2.2, C3.2, C4.2, C5.2, C6.2, C7.2, C8.2, C9.2, C10.2, C11.2, C12.2, C13.2, C14.2, C15.2, H1.1, H2.1, H3.1, H4.1, H5.1, H6.1, J1.1 (A1), J1.31 (A31), J1.32 (B1), J1.62 (B31), J2.1 (A1), J2.31 (A31), J2.32 (B1), J2.62 (B31), J3.1 (A1), J3.31 (A31), J3.32 (B1), J3.62 (B31), J4.1 (A1), J4.31 (A31), J4.32 (B1), J4.62 (B31), J5.1 (A1), J5.31 (A31), J5.32 (B1), J5.62 (B31), J6.1 (A1), J6.31 (A31), J6.32 (B1), J6.62 (B31), J7.1 (A1), J7.31 (A31), J7.32 (B1), J7.62 (B31), J8.1 (A1), J8.31 (A31), J8.32 (B1), J8.62 (B31), J9.17, J10.18, J11.2, J11.3, R1.1, S1.MH1, S1.MH2, U1.1 (GND)
unnamed: D1.1 (K), R1.2
unnamed: J11.1, S1.2 (COM)

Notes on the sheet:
OUT (+)
Green
OUT (-)

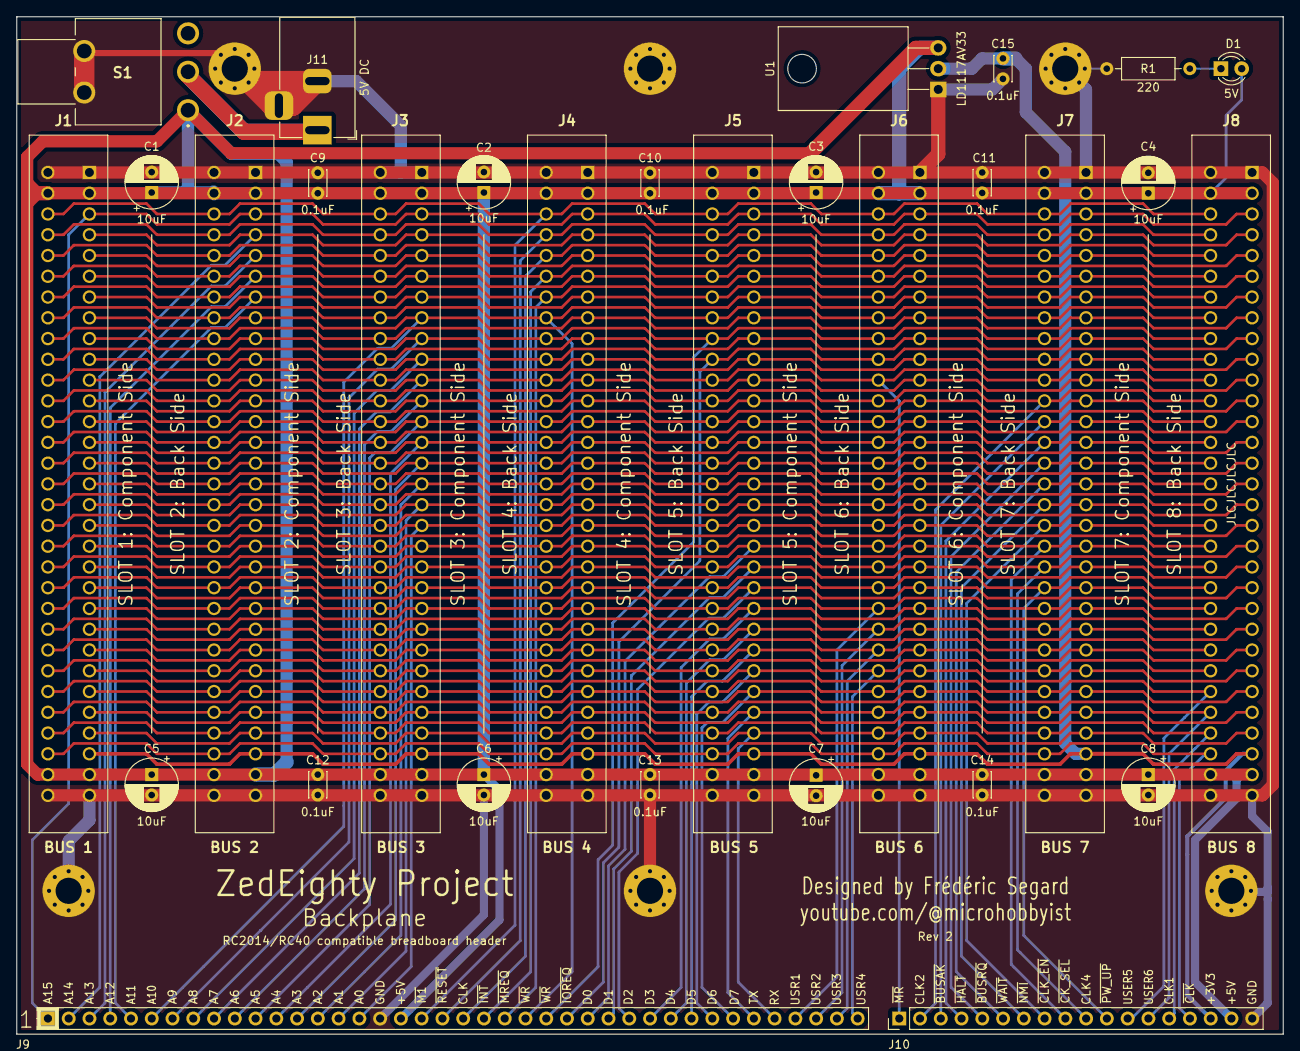
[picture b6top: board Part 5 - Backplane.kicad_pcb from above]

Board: 2 copper layers, 154.9 x 124.5 mm, 36 parts (0 on the bottom side), 58 nets.
